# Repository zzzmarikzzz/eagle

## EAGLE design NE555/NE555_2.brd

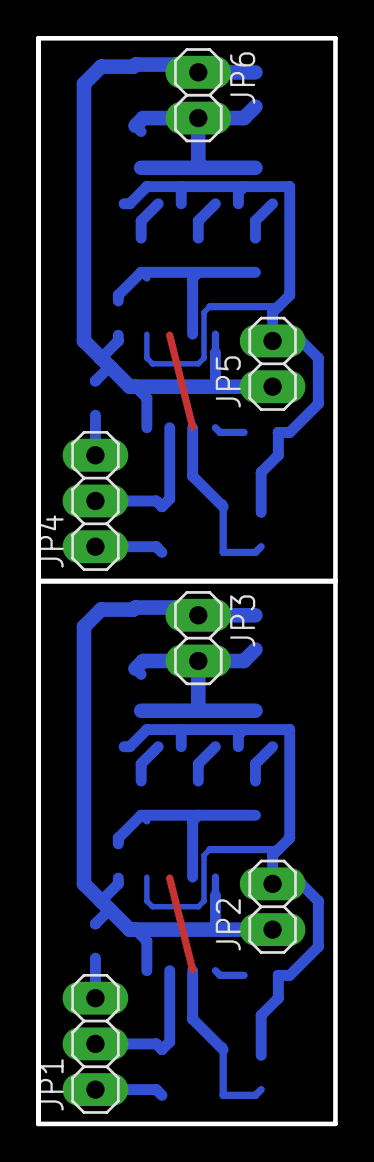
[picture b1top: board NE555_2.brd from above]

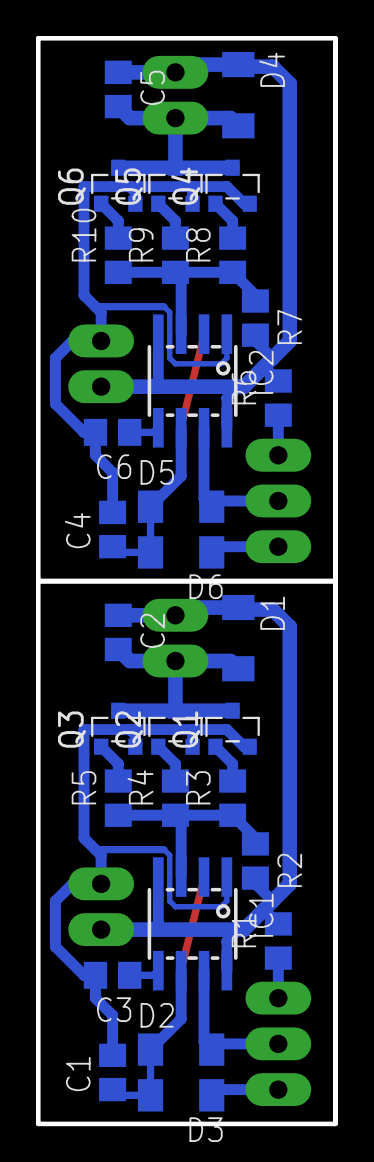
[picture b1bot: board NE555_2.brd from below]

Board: 2 copper layers, 16.5 x 60.3 mm, 36 parts (30 on the bottom side), 24 nets.

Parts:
C1, C4: 2.7nF; C0805
C2, C5: 330nF; C0805
C3, C6: 1nF; C0805
D1, D2, D3, D4, D5, D6: DIODE; SOD80
IC1, IC2: NE555; SO08
JP1, JP4: 1X03
JP2, JP3, JP5, JP6: 1X02
Q1, Q2, Q3, Q4, Q5, Q6: SI2302; SOT-23-GSD
R1, R2, R6, R7: 1k; R0805
R3, R4, R5, R8, R9, R10: 240; R0805

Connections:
GND: C1.2, C3.2, IC1.1, JP2.2, Q1.S, Q2.S, Q3.S
GND1: C4.2, C6.2, IC2.1, JP5.2, Q4.S, Q5.S, Q6.S
unnamed: C2.1, D1.1, IC1.4, IC1.8, JP2.1, JP3.1, R1.2, R2.2
unnamed: IC1.3, R2.1, R3.1, R4.1, R5.1
unnamed: C2.2, D1.2, JP3.2, Q1.D, Q2.D, Q3.D
unnamed: Q1.G, R3.2
unnamed: Q2.G, R4.2
unnamed: Q3.G, R5.2
unnamed: C5.1, D4.1, IC2.4, IC2.8, JP5.1, JP6.1, R6.2, R7.2
unnamed: C3.1, IC1.5
unnamed: C1.1, D2.1, D3.2, IC1.2, IC1.6
unnamed: IC2.3, R7.1, R8.1, R9.1, R10.1
unnamed: D2.2, IC1.7, JP1.2
unnamed: JP1.3, R1.1
unnamed: D3.1, JP1.1
unnamed: C5.2, D4.2, JP6.2, Q4.D, Q5.D, Q6.D
unnamed: Q4.G, R8.2
unnamed: Q5.G, R9.2
unnamed: Q6.G, R10.2
unnamed: C6.1, IC2.5
unnamed: C4.1, D5.1, D6.2, IC2.2, IC2.6
unnamed: D5.2, IC2.7, JP4.2
unnamed: JP4.3, R6.1
unnamed: D6.1, JP4.1

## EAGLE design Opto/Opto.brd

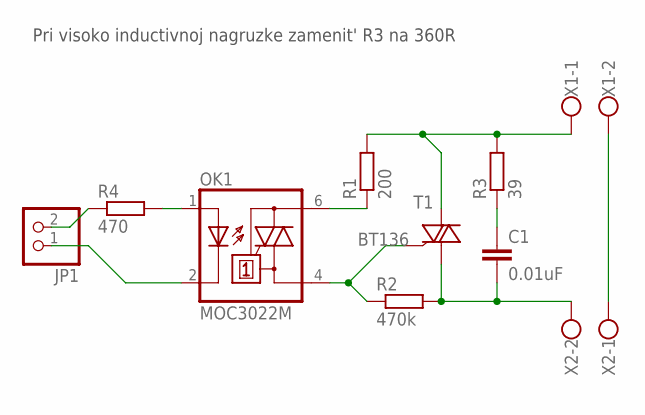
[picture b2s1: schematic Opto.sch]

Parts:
C1: 0.01uF; C102-043X133
JP1: PINHD-1X2/90; 1X02/90
OK1: MOC3022M; DIL06
R1: 200; 0207/2V
R2: 470k; 0207/2V
R3: 39; 0207/2V
R4: 470; R0805
T1: BT136; TO220AB
X1, X2: W237-102

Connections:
unnamed: OK1.4 (A1), R2.1, T1.3 (G)
unnamed: C1.2, R2.2, T1.1 (A1), X2.2
unnamed: OK1.6 (A2), R1.1
unnamed: R1.2, R3.2, T1.2 (A2), X1.1
unnamed: C1.1, R3.1
unnamed: X1.2, X2.1
unnamed: JP1.1, OK1.2 (C)
unnamed: JP1.2, R4.1
unnamed: OK1.1 (A), R4.2

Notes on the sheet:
Pri visoko inductivnoj nagruzke zamenit' R3 na 360R

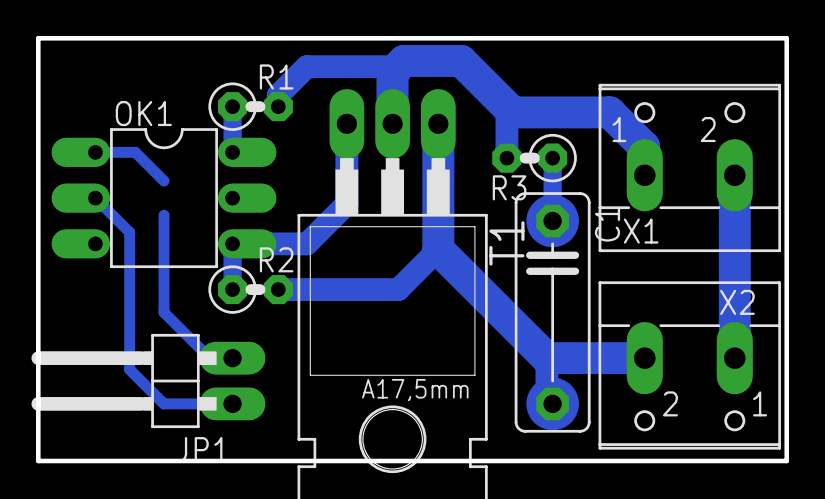
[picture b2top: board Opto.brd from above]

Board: 2 copper layers, 41.6 x 23.5 mm, 10 parts (1 on the bottom side), 9 nets.

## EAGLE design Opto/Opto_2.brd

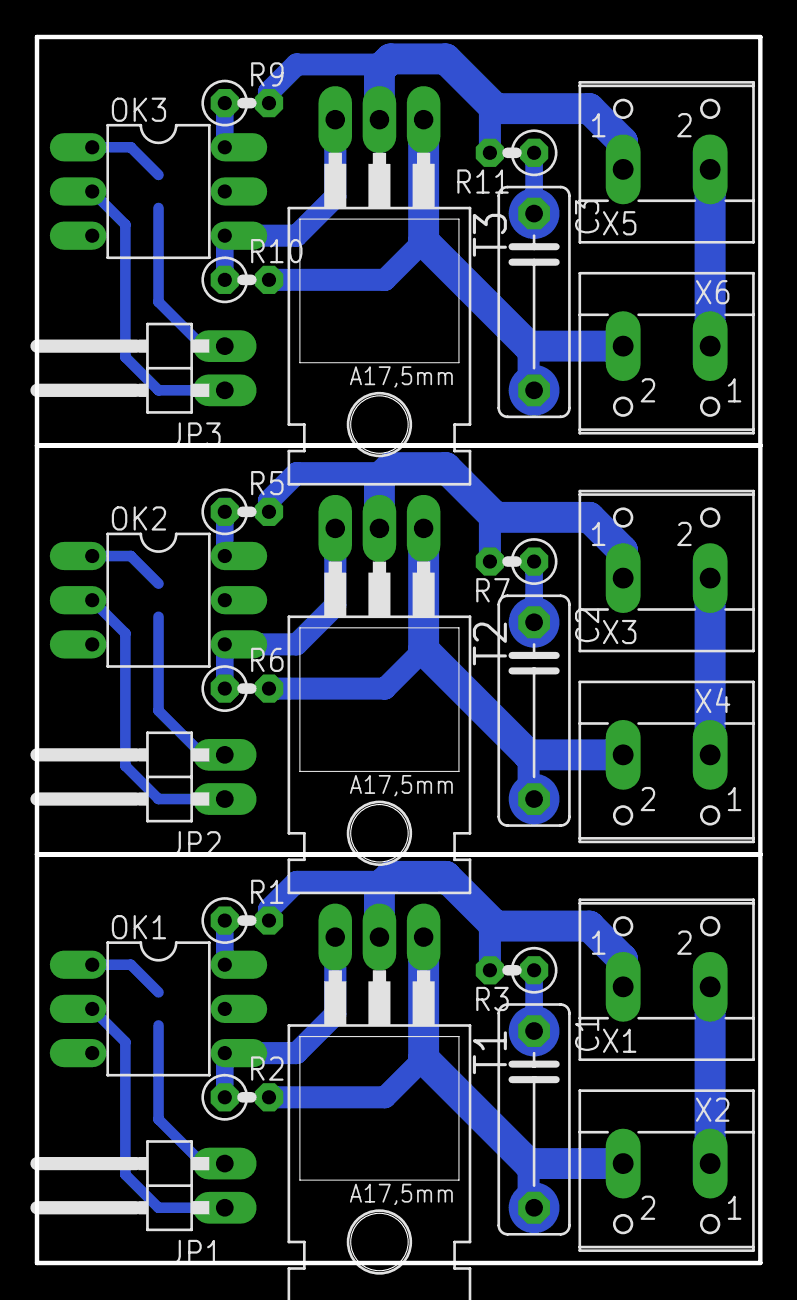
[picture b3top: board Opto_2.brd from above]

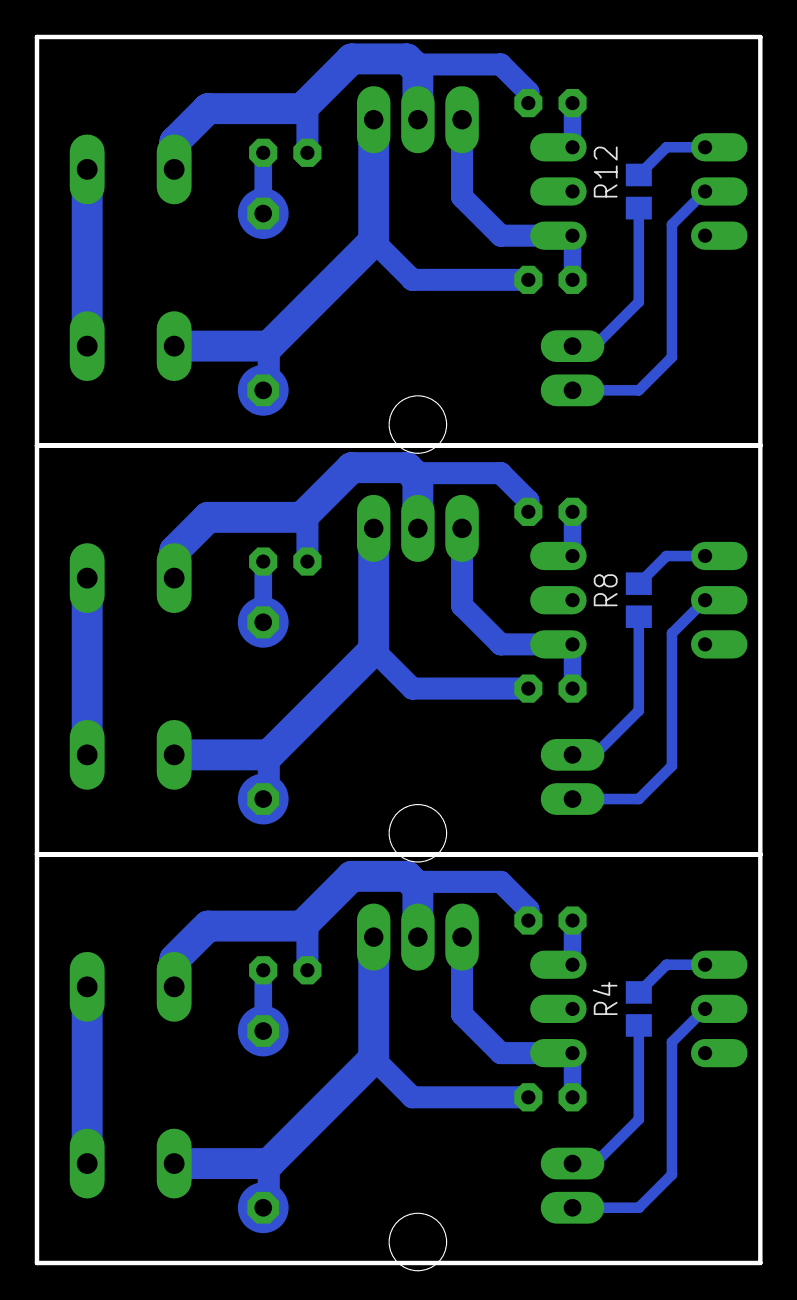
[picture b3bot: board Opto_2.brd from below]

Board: 2 copper layers, 41.6 x 70.5 mm, 30 parts (3 on the bottom side), 27 nets.

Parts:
C1, C2, C3: 0.01uF; C102-043X133
JP1, JP2, JP3: 1X02/90
OK1, OK2, OK3: MOC3022M; DIL06
R1, R5, R9: 200; 0207/2V
R2, R6, R10: 470k; 0207/2V
R3, R7, R11: 39; 0207/2V
R4, R8, R12: 470; R0805
T1, T2, T3: BT136; TO220AB
X1, X2, X3, X4, X5, X6: W237-102

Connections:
unnamed: OK1.4, R2.1, T1.3
unnamed: C1.2, R2.2, T1.1, X2.2
unnamed: OK1.6, R1.1
unnamed: R1.2, R3.2, T1.2, X1.1
unnamed: C1.1, R3.1
unnamed: X1.2, X2.1
unnamed: JP1.1, OK1.2
unnamed: JP1.2, R4.1
unnamed: OK1.1, R4.2
unnamed: OK2.4, R6.1, T2.3
unnamed: C2.2, R6.2, T2.1, X4.2
unnamed: OK2.6, R5.1
unnamed: R5.2, R7.2, T2.2, X3.1
unnamed: C2.1, R7.1
unnamed: JP2.1, OK2.2
unnamed: JP2.2, R8.1
unnamed: OK2.1, R8.2
unnamed: X3.2, X4.1
unnamed: OK3.4, R10.1, T3.3
unnamed: C3.2, R10.2, T3.1, X6.2
unnamed: OK3.6, R9.1
unnamed: R9.2, R11.2, T3.2, X5.1
unnamed: C3.1, R11.1
unnamed: JP3.1, OK3.2
unnamed: JP3.2, R12.1
unnamed: OK3.1, R12.2
unnamed: X5.2, X6.1

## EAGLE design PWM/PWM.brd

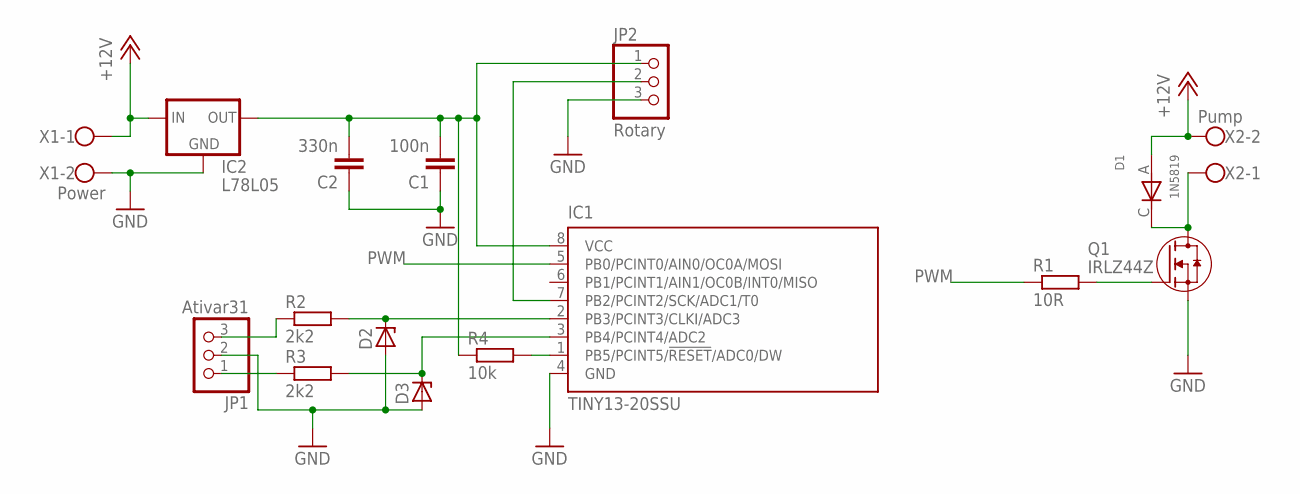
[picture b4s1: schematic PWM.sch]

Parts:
C1: 100n; C0805
C2: 330n; C0805
D1: 1N5819; DO214AC
D2, D3: ZENER-DIODESOD80C; SOD80C
IC1: TINY13-20SSU; 8S1
IC2: L78L05; 78LXX
JP1: Ativar31; 1X03
JP2: Rotary; 1X03
Q1: IRLZ44Z; TO220AV
R1: 10R; R0805
R2, R3: 2k2; R0805
R4: 10k; R0805
X1: Power; W237-102
X2: Pump; W237-102

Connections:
+12V: D1.A (ANOD), IC2.IN, X1.1, X2.2
GND: C1.1, C2.1, D2.A, D3.A, IC1.4 (GND), IC2.GND, JP1.2, JP2.3, Q1.3 (S), X1.2
unnamed: C1.2, C2.2, IC1.8 (VCC), IC2.OUT, JP2.1, R4.1
unnamed: D1.C (KATOD), Q1.2 (D), X2.1
unnamed: Q1.1 (G), R1.2
unnamed: JP1.3, R2.1
unnamed: JP1.1, R3.1
unnamed: D2.C, IC1.2 (PB3/PCINT3/CLKI/ADC3), R2.2
unnamed: D3.C, IC1.3 (PB4/PCINT4/ADC2), R3.2
unnamed: IC1.1 (PB5/PCINT5/!RESET!/ADC0/DW), R4.2
unnamed: IC1.7 (PB2/PCINT2/SCK/ADC1/T0), JP2.2
PWM: IC1.5 (PB0/PCINT0/AIN0/OC0A/MOSI), R1.1

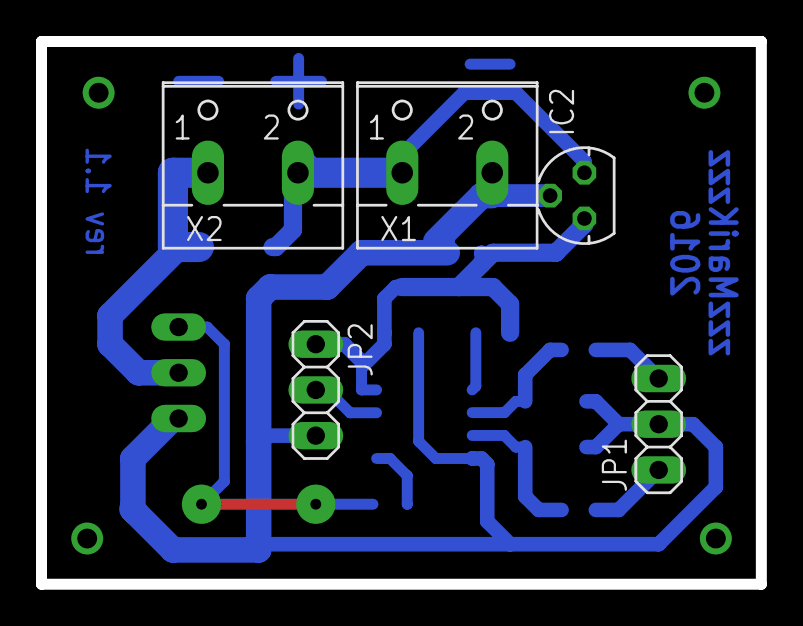
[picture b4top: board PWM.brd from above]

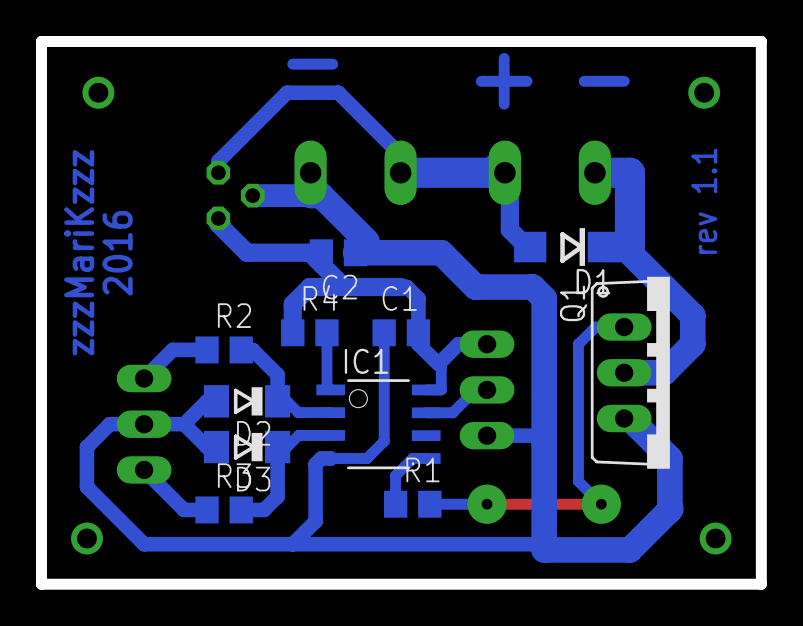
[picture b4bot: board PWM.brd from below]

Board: 2 copper layers, 40.0 x 30.2 mm, 16 parts (11 on the bottom side), 12 nets.

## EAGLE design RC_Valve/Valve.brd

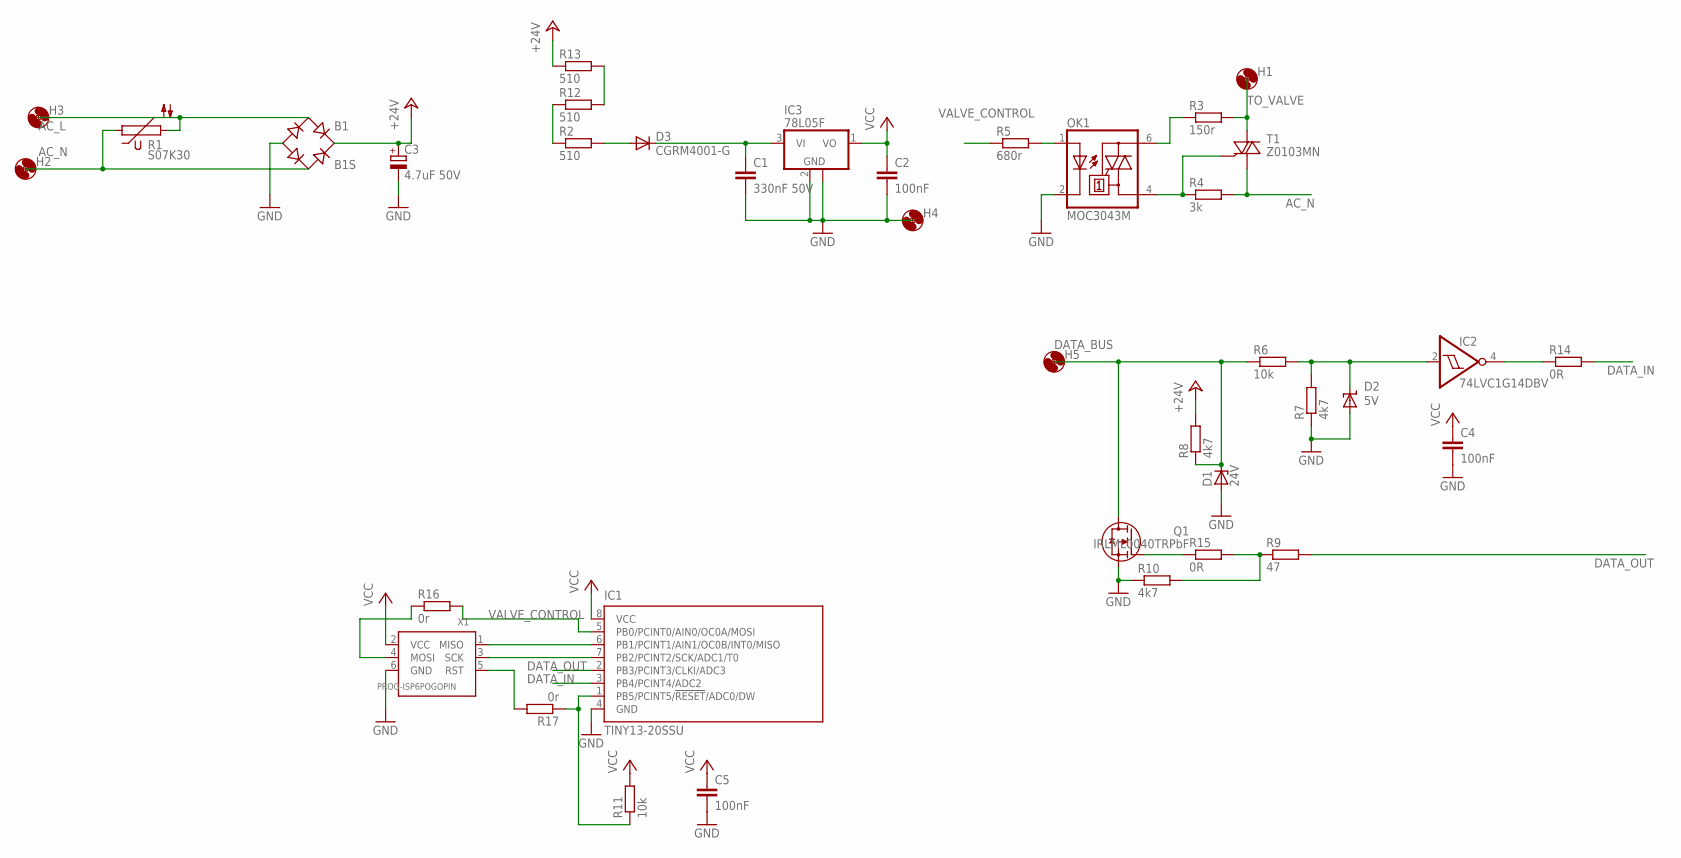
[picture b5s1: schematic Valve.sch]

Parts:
B1: B1S; MBS
C1: 330nF 50V; C0805K
C2, C5: 100nF; C0805K
C3: 4.7uF 50V; D/7343-31R
C4: 100nF; 0805
D1: 24V; SOT23
D2: 5V; SOD123
D3: CGRM4001-G; SOD-123_MINI-SMA
H1, H2, H3, H4, H5: MOUNT-HOLE3.0; 3,0
IC1: TINY13-20SSU; 8S1
IC2: 74LVC1G14DBV; SOT23-5
IC3: 78L05F; SOT89
OK1: MOC3043M; DIL06
Q1: IRLML0040TRPbF; SOT-23-GSD
R1: S07K30; S07K40
R2, R12, R13: 510; R2512
R3: 150r; R0805
R4: 3k; R0805
R5: 680r; R0805
R6, R11: 10k; R0805
R7, R8, R10: 4k7; R0805
R9: 47; R0805
R14, R15: 0R; R1206W
R16, R17: 0r; 0805R
T1: Z0103MN; SOT223
X1: PROG-ISP6POGOPIN; PROG_POGOPIN

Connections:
+24V: B1.+, C3.+, R8.2, R13.1
AC_L: B1.AC1, H3.P$1, R1.2
AC_N: B1.AC2, H2.P$1, R1.1, R4.2, T1.1 (A1)
DATA_BUS: D1.3 (C), H5.P$1, Q1.D, R6.1, R8.1
DATA_IN: IC1.3 (PB4/PCINT4/ADC2), R14.2
DATA_OUT: IC1.2 (PB3/PCINT3/CLKI/ADC3), R9.2
GND: B1.-, C1.2, C2.2, C3.-, C4.2, C5.2, D1.1 (A), D2.A, H4.P$1, IC1.4 (GND), IC2.3 (GND), IC3.2 (GND), IC3.2@1 (GND), OK1.2 (C), Q1.S, R7.1, R10.1, X1.6 (GND)
unnamed: C1.1, D3.C, IC3.3 (VI)
unnamed: D3.A, R2.2
unnamed: R12.2, R13.2
unnamed: OK1.4 (A1), R4.1, T1.3 (G)
unnamed: R2.1, R12.1
unnamed: D2.C, IC2.2 (I), R6.2, R7.2
unnamed: R9.1, R10.2, R15.2
unnamed: IC1.1 (PB5/PCINT5/!RESET!/ADC0/DW), R11.1, R17.1
unnamed: IC2.4 (O), R14.1
unnamed: IC1.6 (PB1/PCINT1/AIN1/OC0B/INT0/MISO), X1.1 (MISO)
unnamed: IC1.7 (PB2/PCINT2/SCK/ADC1/T0), X1.3 (SCK)
unnamed: Q1.G, R15.1
unnamed: R16.1, X1.4 (MOSI)
unnamed: R17.2, X1.5 (RST)
unnamed: OK1.1 (A), R5.2
unnamed: OK1.6 (A2), R3.1
TO_VALVE: H1.P$1, R3.2, T1.2 (A2), T1.4 (A2)
VALVE_CONTROL: IC1.5 (PB0/PCINT0/AIN0/OC0A/MOSI), R5.1, R16.2
VCC: C2.1, C4.1, C5.1, IC1.8 (VCC), IC2.5 (VCC), IC3.1 (VO), R11.2, X1.2 (VCC)

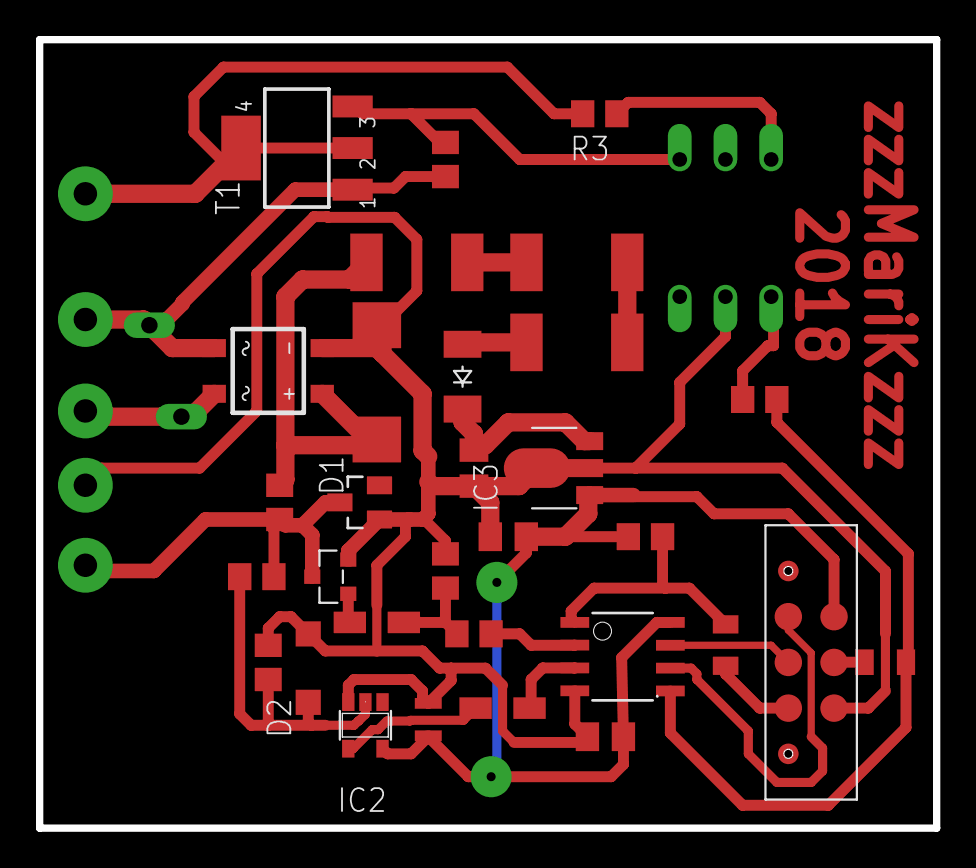
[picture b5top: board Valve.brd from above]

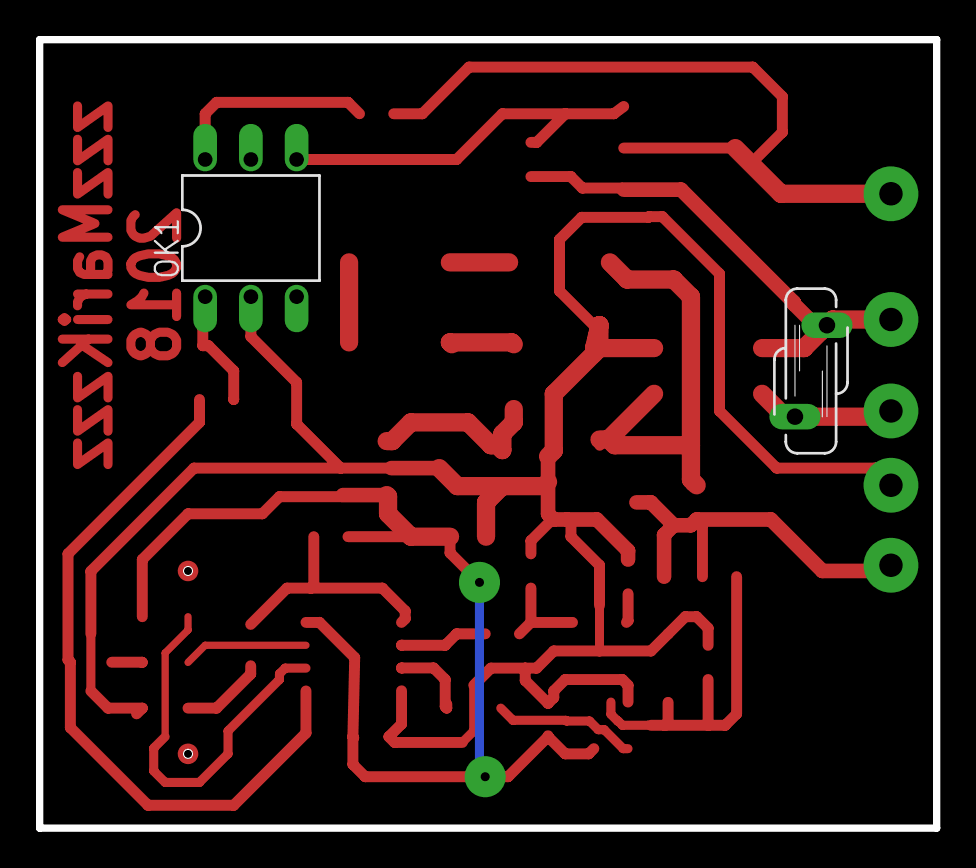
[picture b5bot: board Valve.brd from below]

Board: 2 copper layers, 49.8 x 43.8 mm, 38 parts (2 on the bottom side), 26 nets.

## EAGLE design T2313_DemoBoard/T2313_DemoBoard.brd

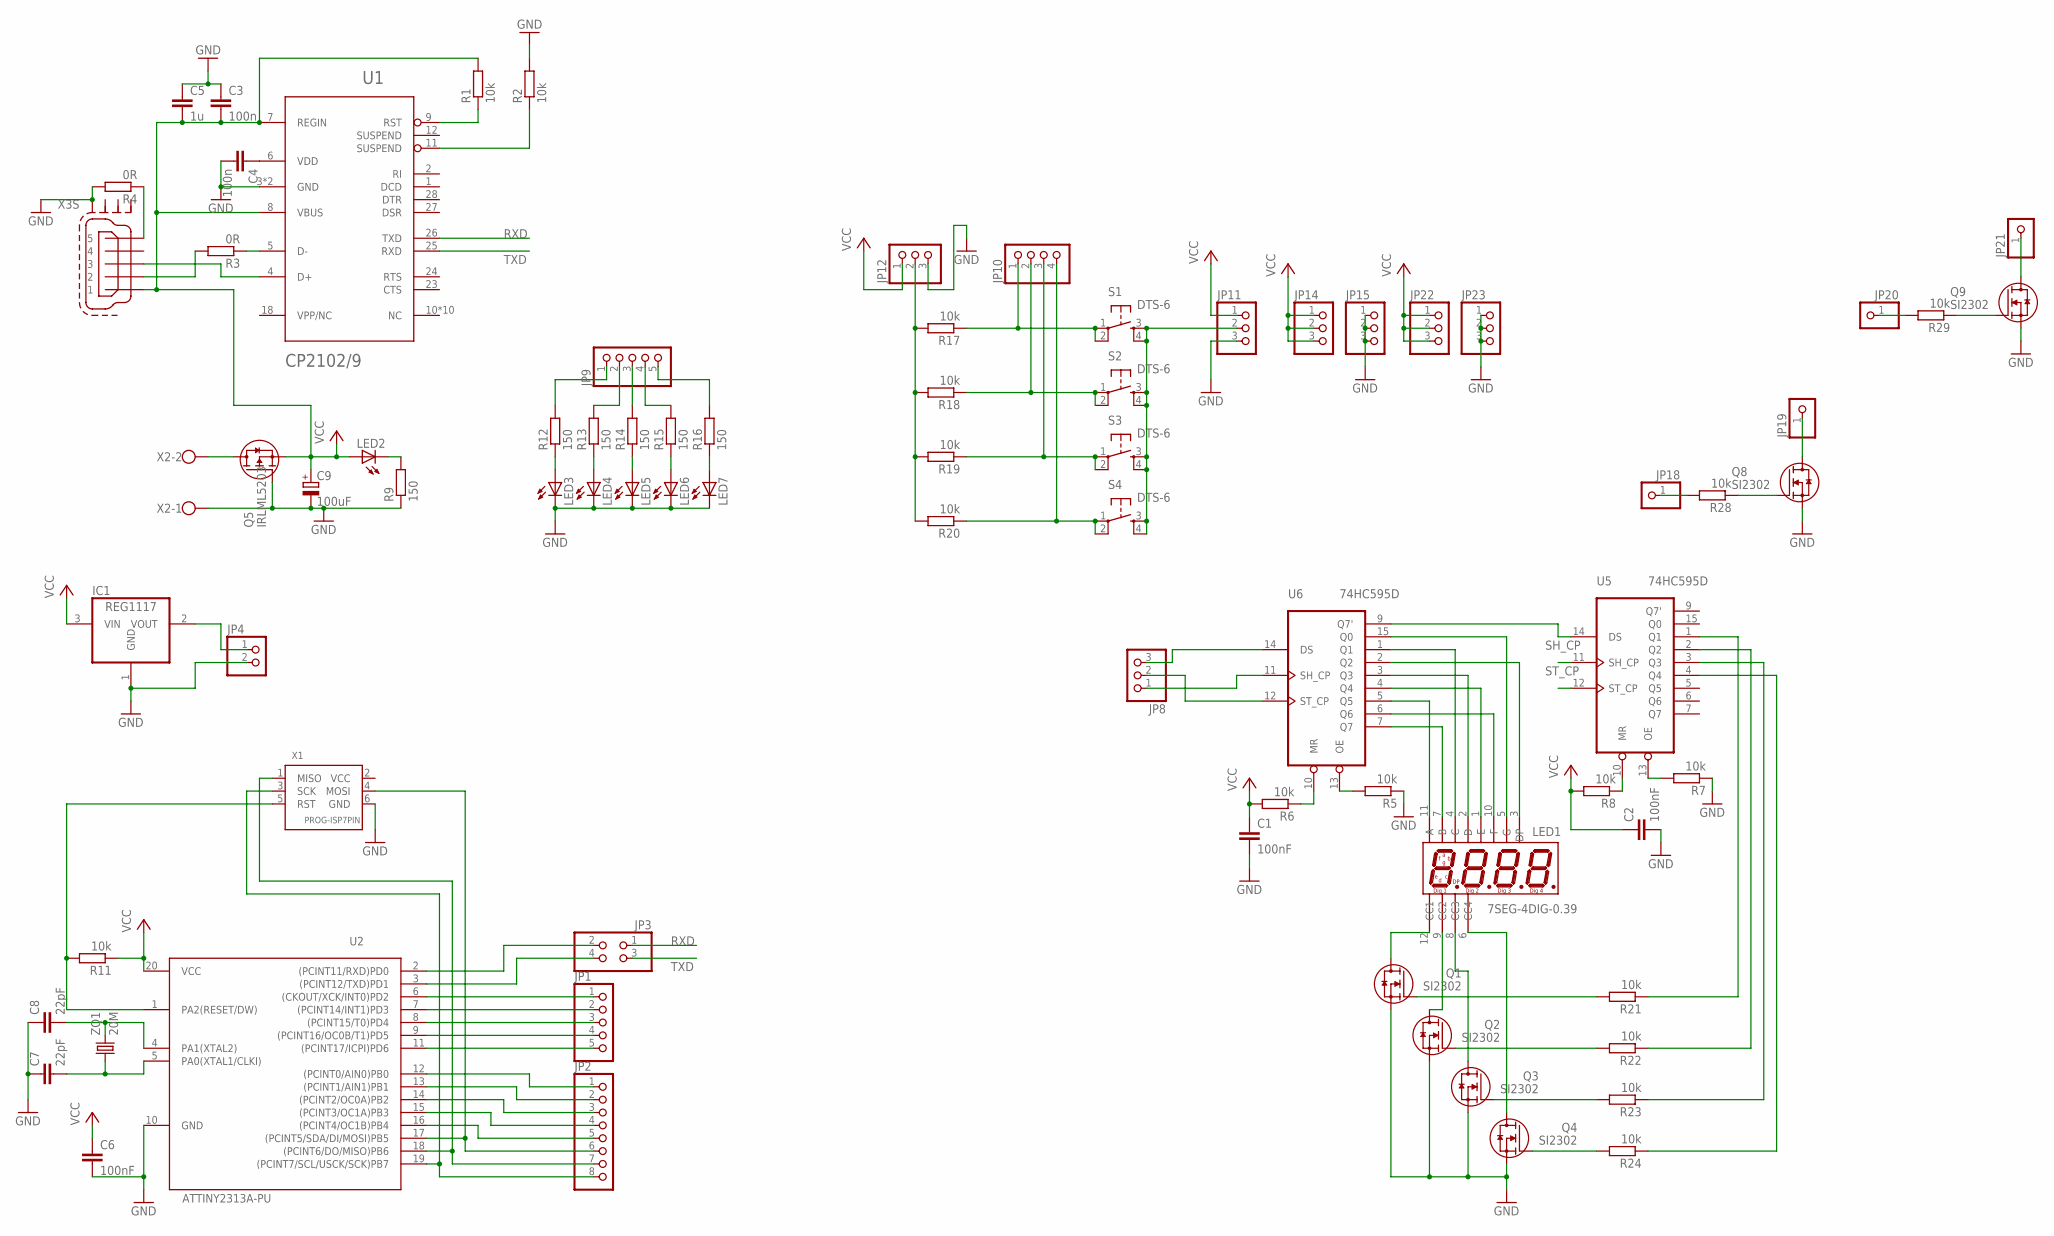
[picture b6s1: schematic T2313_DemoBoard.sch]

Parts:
C1, C2, C6: 100nF; C0603
C3, C4: 100n; C0603
C5: 1u; C0805
C7, C8: 22pF; C0603
C9: 100uF; E2-5
IC1: REG1117; SOT223
JP1, JP9: PINHD-1X5; 1X05
JP2: PINHD-1X8; 1X08
JP3: PINHD-2X2; 2X02
JP4: PINHD-1X2; 1X02
JP8, JP11, JP12, JP14, JP15, JP22, JP23: PINHD-1X3; 1X03
JP10: PINHD-1X4; 1X04
JP18, JP19, JP20, JP21: PINHD-1X1; 1X01
LED1: 7SEG-4DIG-0.39; 7SEG_4DIG_0.39
LED2: LEDSML0805; SML0805
LED3, LED4, LED5, LED6, LED7: LEDCHIPLED_0805; CHIPLED_0805
Q1, Q2, Q3, Q4, Q8, Q9: SI2302; SOT-23-GSD
Q5: IRLML5203; SOT-23-GSD
R1, R2: 10k; R0603
R3, R4: 0R; R0805
R5, R6, R7, R8, R11, R17, R18, R19, R20, R21, R22, R23, R24, R28, R29: 10k; R0805
R9, R12, R13, R14, R15, R16: 150; R0805
S1, S2, S3, S4: DTS-6
U1: CP2102/9; QFN-28
U2: ATTINY2313A-PU; DIL20
U5, U6: 74HC595D; SO16
X1: PROG-ISP7PIN; PROG_PIN
X2: W237-102
X3: MINI-USB-SCHIELD-32005-201; 32005-201
ZQ1: 20M; HC49/S

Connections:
GND: C1.2, C2.2, C3.1, C4.2, C5.1, C6.2, C7.1, C8.1, C9.-, IC1.1 (GND), JP4.2, JP11.3, JP12.3, JP15.1, JP15.2, JP15.3, JP23.1, JP23.2, JP23.3, LED3.C, LED4.C, LED5.C, LED6.C, LED7.C, Q1.S, Q2.S, Q3.S, Q4.S, Q5.G, Q8.S, Q9.S, R2.2, R4.2, R5.1, R7.1, R9.1, U1.3 (GND), U1.P$29 (GND), U2.10 (GND), U5.8 (GND), U6.8 (GND), X1.6 (GND), X2.1, X3.M4 (S4)
unnamed: JP1.5, U2.11 ((PCINT17/ICPI)PD6)
unnamed: JP1.4, U2.9 ((PCINT16/OC0B/T1)PD5)
unnamed: JP1.3, U2.8 ((PCINT15/T0)PD4)
unnamed: JP1.2, U2.7 ((PCINT14/INT1)PD3)
unnamed: JP1.1, U2.6 ((CKOUT/XCK/INT0)PD2)
unnamed: JP3.4, U2.3 ((PCINT12/TXD)PD1)
unnamed: JP3.2, U2.2 ((PCINT11/RXD)PD0)
unnamed: R6.1, U6.10 (MR)
unnamed: JP2.7, U2.18 ((PCINT6/DO/MISO)PB6), X1.1 (MISO)
unnamed: C4.1, U1.6 (VDD)
unnamed: JP2.5, U2.16 ((PCINT4/OC1B)PB4)
unnamed: JP2.4, U2.15 ((PCINT3/OC1A)PB3)
unnamed: JP2.3, U2.14 ((PCINT2/OC0A)PB2)
unnamed: JP2.2, U2.13 ((PCINT1/AIN1)PB1)
unnamed: JP2.1, U2.12 ((PCINT0/AIN0)PB0)
unnamed: R1.1, U1.9 (RST)
unnamed: R3.2, X3.2
unnamed: U1.4 (D+), X3.3
unnamed: R5.2, U6.13 (OE)
unnamed: R2.1, U1.11 (SUSPEND)
unnamed: R8.1, U5.10 (MR)
unnamed: R3.1, U1.5 (D-)
unnamed: IC1.2 (VOUT), JP4.1
unnamed: R7.2, U5.13 (OE)
unnamed: R4.1, X3.5
unnamed: JP8.3, U6.14 (DS)
unnamed: LED1.11 (A), U6.5 (Q5)
unnamed: LED1.7 (B), U6.7 (Q7)
unnamed: U5.14 (DS), U6.9 (Q7')
unnamed: LED1.4 (C), U6.1 (Q1)
unnamed: LED1.2 (D), U6.3 (Q3)
unnamed: LED1.1 (E), U6.4 (Q4)
unnamed: LED1.10 (F), U6.6 (Q6)
unnamed: LED1.5 (G), U6.15 (Q0)
unnamed: LED1.3 (DP), U6.2 (Q2)
unnamed: LED1.12 (CC1), Q1.D
unnamed: LED1.9 (CC2), Q2.D
unnamed: LED1.8 (CC3), Q3.D
unnamed: LED1.6 (CC4), Q4.D
unnamed: R21.1, U5.1 (Q1)
unnamed: R22.1, U5.2 (Q2)
unnamed: R23.1, U5.3 (Q3)
unnamed: R24.1, U5.4 (Q4)
unnamed: C7.2, U2.5 (PA0(XTAL1/CLKI)), ZQ1.1
unnamed: C8.2, U2.4 (PA1(XTAL2)), ZQ1.2
unnamed: R11.2, U2.1 (PA2(RESET/DW)), X1.5 (RST)
unnamed: LED2.C, R9.2
unnamed: LED3.A, R12.1
unnamed: LED4.A, R13.1
unnamed: LED5.A, R14.1
unnamed: LED6.A, R15.1
unnamed: LED7.A, R16.1
unnamed: JP9.1, R12.2
unnamed: JP9.3, R14.2
unnamed: JP9.4, R15.2
unnamed: JP9.2, R13.2
unnamed: JP9.5, R16.2
unnamed: JP10.2, R18.1, S2.1, S2.2
unnamed: JP12.2, R17.2, R18.2, R19.2, R20.2
unnamed: JP10.1, R17.1, S1.1, S1.2
unnamed: JP11.2, S1.3, S1.4, S2.3, S2.4, S3.3, S3.4, S4.3, S4.4
unnamed: JP10.3, R19.1, S3.1, S3.2
unnamed: JP10.4, R20.1, S4.1, S4.2
unnamed: Q4.G, R24.2
unnamed: Q3.G, R23.2
unnamed: Q2.G, R22.2
unnamed: Q1.G, R21.2
unnamed: Q5.D, X2.2
unnamed: JP19.1, Q8.D
unnamed: Q8.G, R28.1
unnamed: JP18.1, R28.2
unnamed: JP21.1, Q9.D
unnamed: Q9.G, R29.1
unnamed: JP20.1, R29.2
RXD: JP3.1, U1.26 (TXD)
SCL: JP2.8, U2.19 ((PCINT7/SCL/USCK/SCK)PB7), X1.3 (SCK)
SDA: JP2.6, U2.17 ((PCINT5/SDA/DI/MOSI)PB5), X1.4 (MOSI)
SH_CP: JP8.1, U5.11 (SH_CP), U6.11 (SH_CP)
ST_CP: JP8.2, U5.12 (ST_CP), U6.12 (ST_CP)
TXD: JP3.3, U1.25 (RXD)
VCC: C1.1, C2.1, C3.2, C5.2, C6.1, C9.+, IC1.3 (VIN), JP11.1, JP12.1, JP14.1, JP14.2, JP14.3, JP22.1, JP22.2, JP22.3, LED2.A, Q5.S, R1.2, R6.2, R8.2, R11.1, U1.7 (REGIN), U1.8 (VBUS), U2.20 (VCC), U5.16 (VCC), U6.16 (VCC), X3.1

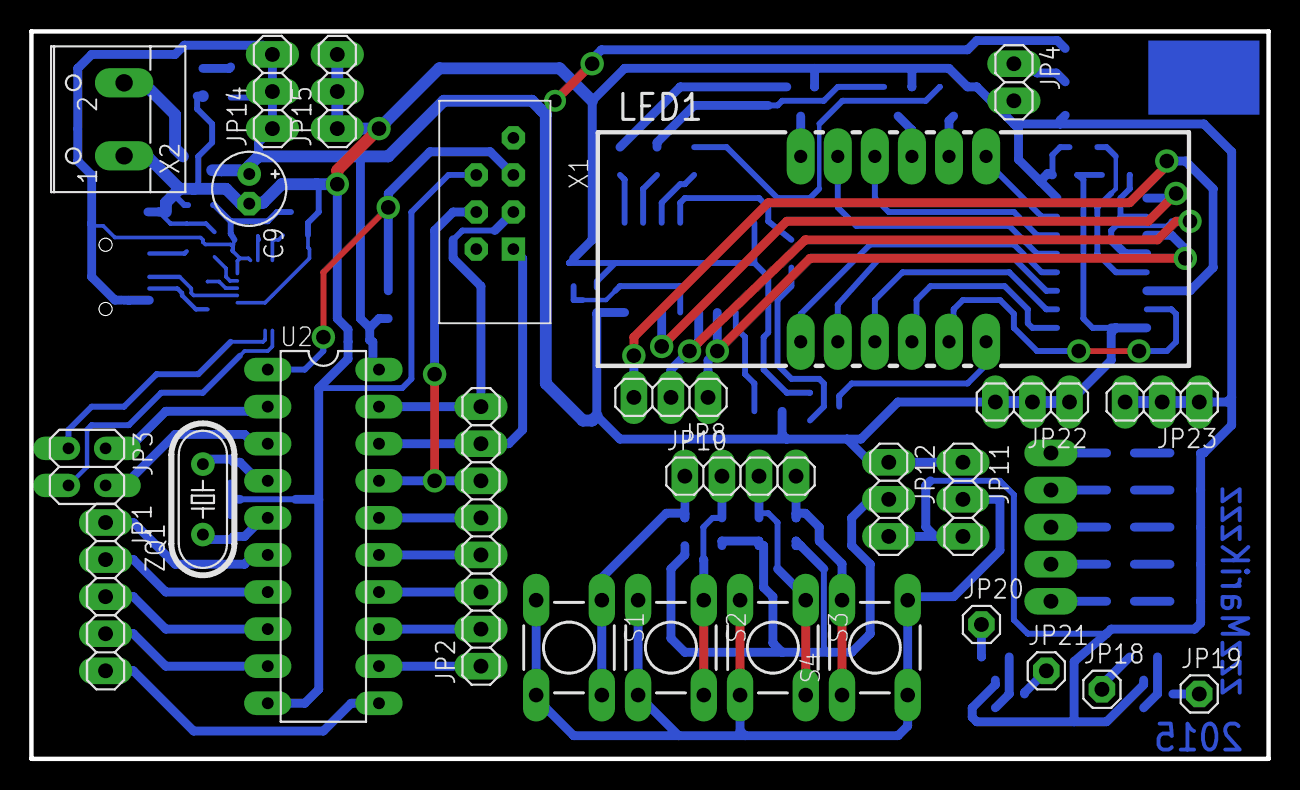
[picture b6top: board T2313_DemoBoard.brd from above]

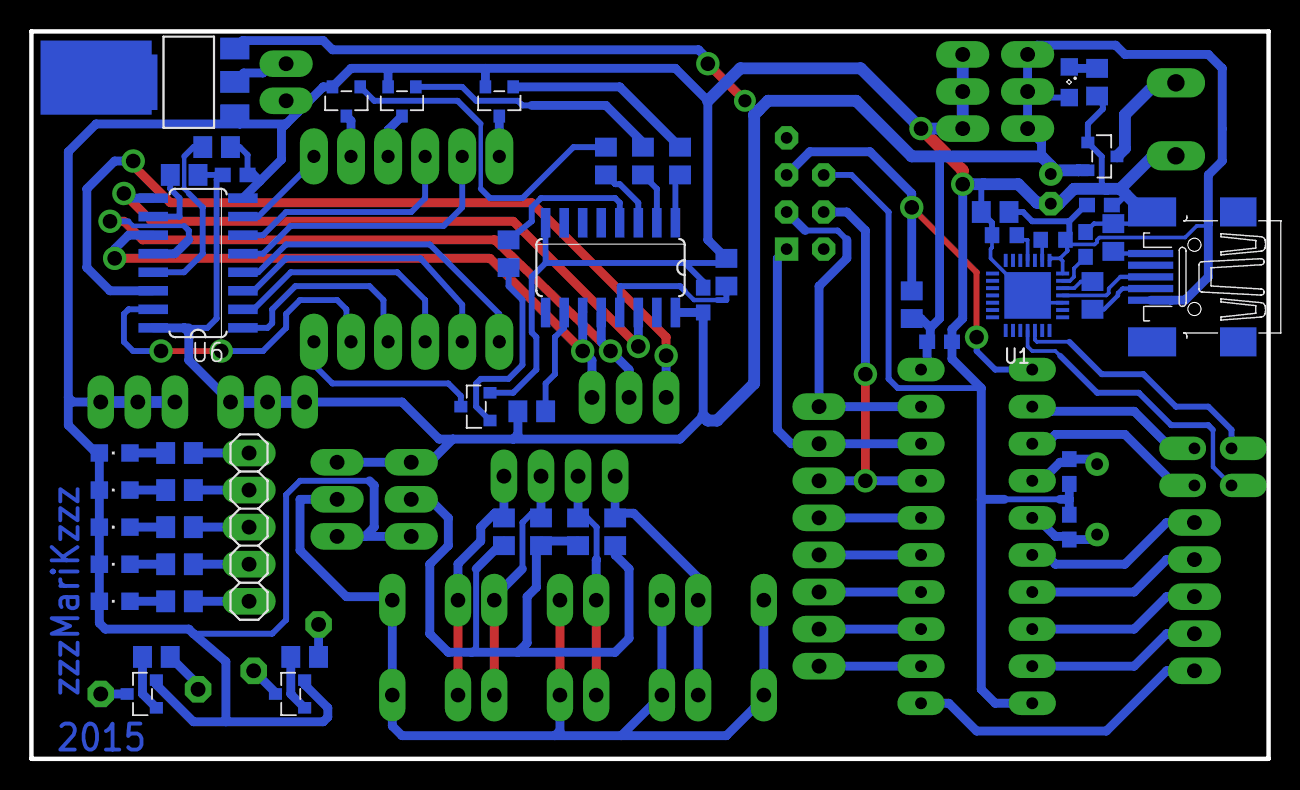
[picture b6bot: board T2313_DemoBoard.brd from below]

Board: 2 copper layers, 84.8 x 49.8 mm, 78 parts (52 on the bottom side), 82 nets.
